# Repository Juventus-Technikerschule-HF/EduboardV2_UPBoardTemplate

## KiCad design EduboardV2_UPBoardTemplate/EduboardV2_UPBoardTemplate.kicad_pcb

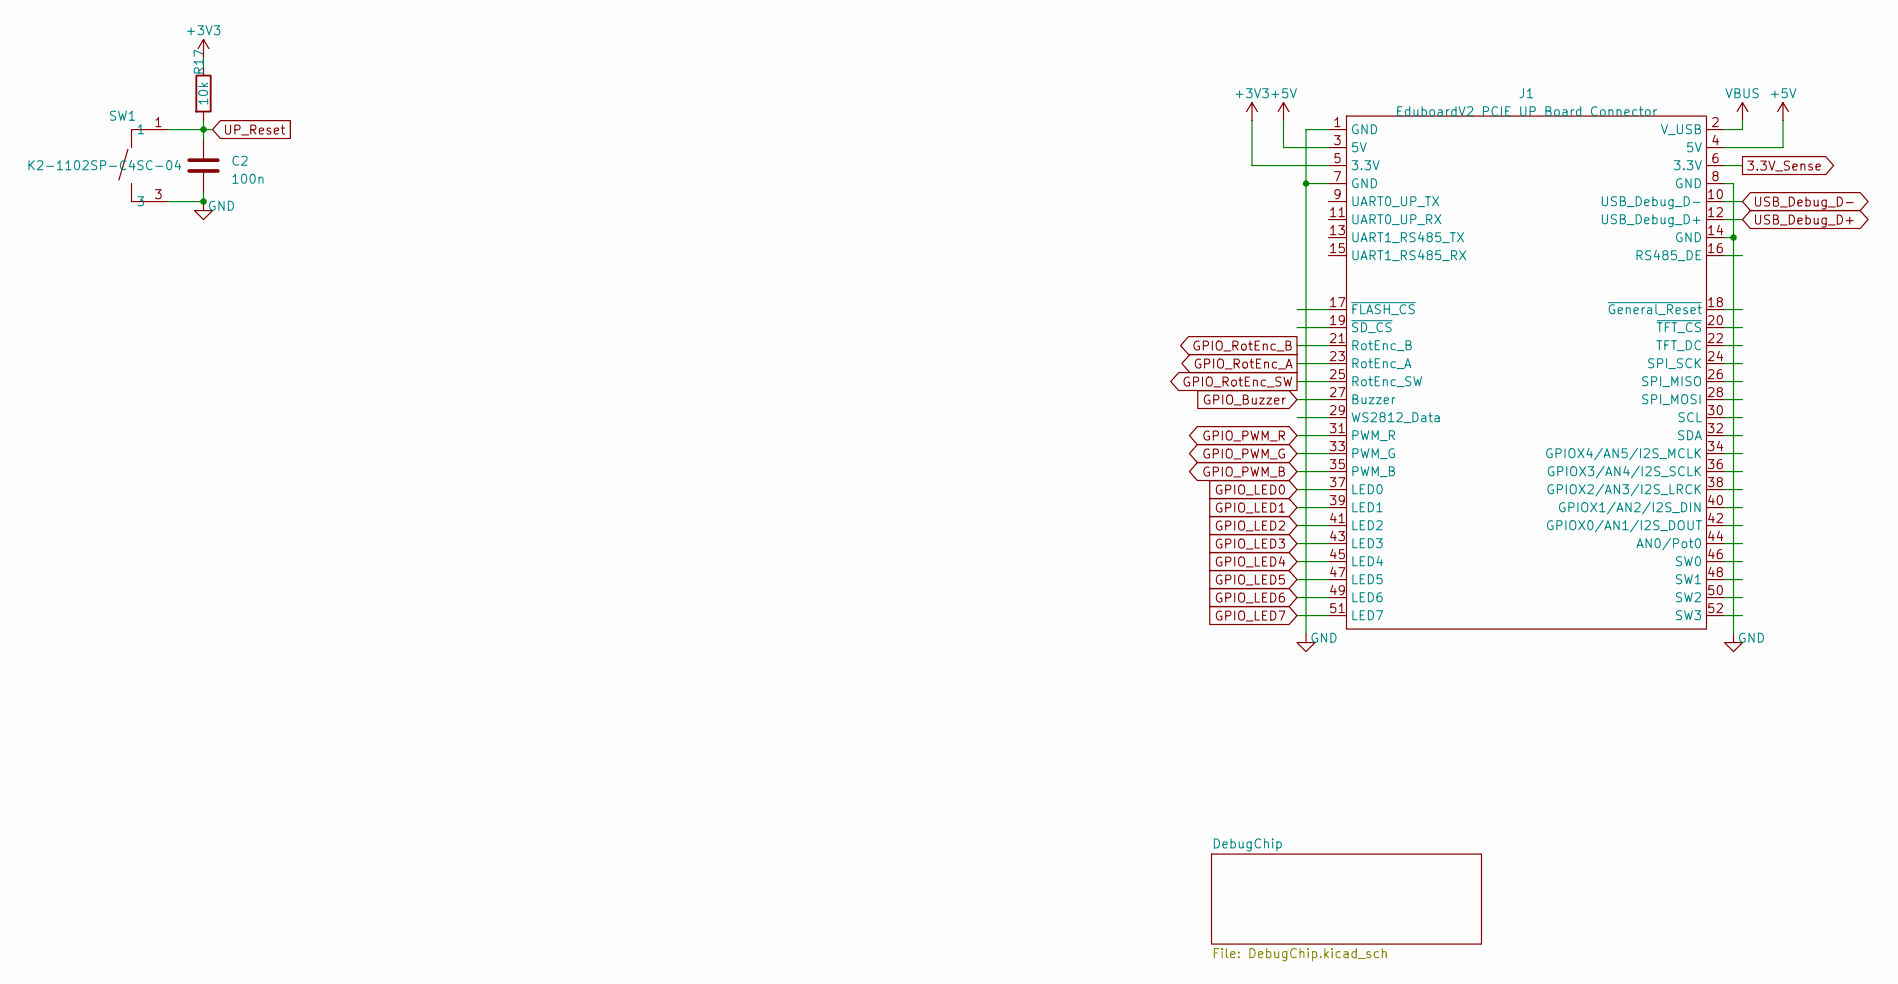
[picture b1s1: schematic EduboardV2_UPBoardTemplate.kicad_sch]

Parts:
C2: 100n; C_0603_1608Metric; JLCPCB Part # C105907
J1: EduboardV2 PCIE UP Board Connector; mini-PCIe_F1_Full
R17: 10k; R_0603_1608Metric; JLCPCB Part # C116677
SW1: K2-1102SP-C4SC-04; KEY-SMD_4P-L6.0-W6.0-P4.50-LS9.5-BL; LCSC Part C127509

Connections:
3.3V_Sense: J1.6 (3.3V); also elsewhere on the board
+3V3: J1.5 (3.3V); also elsewhere on the board
+5V: J1.3 (5V), J1.4 (5V)
GND: J1.1 (GND), J1.7 (GND), J1.8 (GND), J1.14 (GND), SW1.3, SW1.4; also elsewhere on the board
GPIO_Buzzer: J1.27 (Buzzer)
GPIO_LED0: J1.37 (LED0)
GPIO_LED1: J1.39 (LED1)
GPIO_LED2: J1.41 (LED2)
GPIO_LED3: J1.43 (LED3)
GPIO_LED4: J1.45 (LED4)
GPIO_LED5: J1.47 (LED5)
GPIO_LED6: J1.49 (LED6)
GPIO_LED7: J1.51 (LED7)
GPIO_PWM_B: J1.35 (PWM_B)
GPIO_PWM_G: J1.33 (PWM_G)
GPIO_PWM_R: J1.31 (PWM_R)
GPIO_RotEnc_A: J1.23 (RotEnc_A)
GPIO_RotEnc_B: J1.21 (RotEnc_B)
GPIO_RotEnc_SW: J1.25 (RotEnc_SW)
UP_Reset: SW1.1, SW1.2; also elsewhere on the board
USB_Debug_D+: J1.12 (USB_Debug_D+); also elsewhere on the board
USB_Debug_D-: J1.10 (USB_Debug_D-); also elsewhere on the board
VBUS: J1.2 (V_USB); also elsewhere on the board

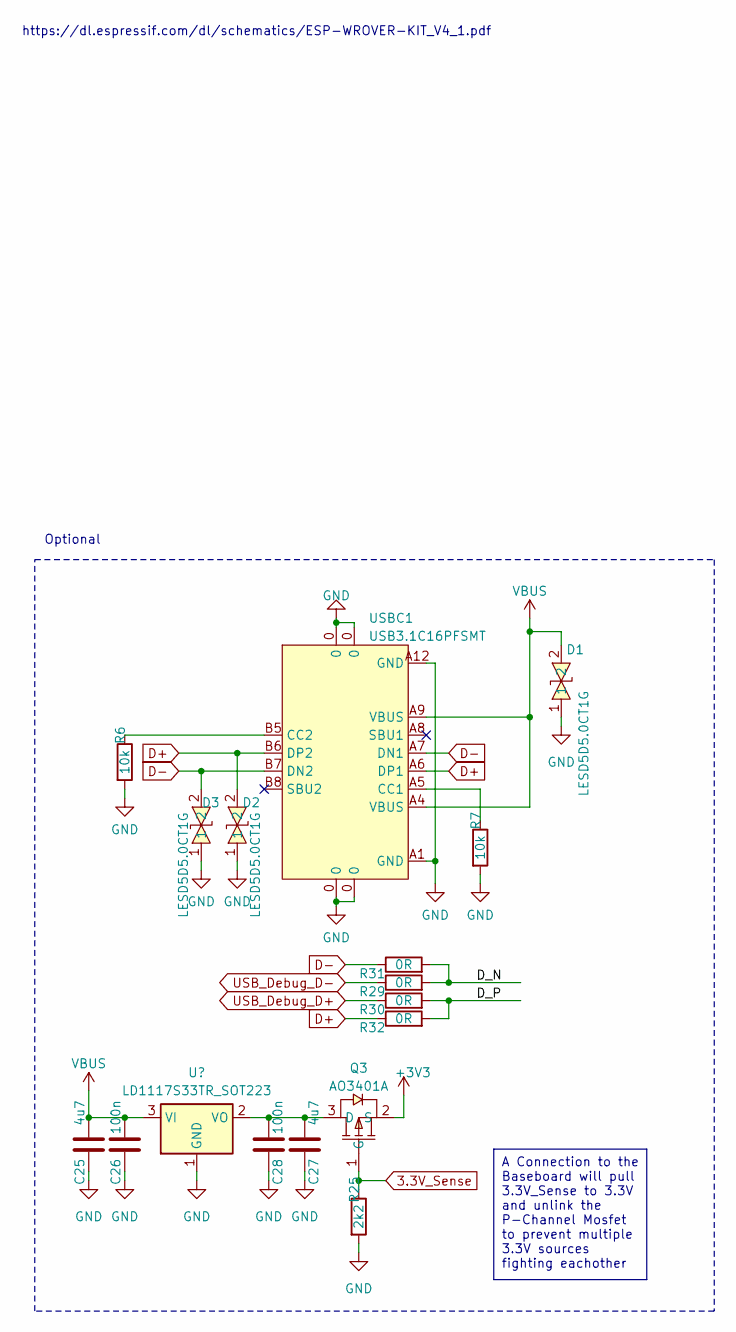
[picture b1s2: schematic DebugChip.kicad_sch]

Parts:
C25, C27: 4u7; C_0805_2012Metric; JLCPCB Part # C76642
C26, C28: 100n; C_0603_1608Metric; JLCPCB Part # C105907
D1, D2, D3: LESD5D5.0CT1G; SOD-523_L1.2-W0.8-LS1.6-BI; LCSC Part C383211
Q3: AO3401A; SOT-23_L2.9-W1.3-P1.90-LS2.4-BR; MPN AO3401A; LCSC Part C15127
R6, R7: 10k; R_0603_1608Metric; JLCPCB Part # C116677
R25: 2k2; R_0603_1608Metric; JLCPCB Part # C115003
R29, R30, R31, R32: 0R; R_0603_1608Metric; JLCPCB Part # C465460
U5: LD1117S33TR_SOT223; SOT-223-3_TabPin2; JLCPCB Part # C86781
USBC1: USB3.1C16PFSMT; USB-C-SMD_TYPE-C-USB-17; LCSC Part C167321

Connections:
3.3V_Sense: Q3.1 (G), R25.1; also elsewhere on the board
+3V3: Q3.2 (S); also elsewhere on the board
/DebugChip/D_N: R29.2, R31.2
/DebugChip/D_P: R30.2, R32.2
D+: D2.2, R32.1, USBC1.A6 (DP1), USBC1.B6 (DP2)
D-: D3.2, R31.1, USBC1.A7 (DN1), USBC1.B7 (DN2)
GND: C25.1, C26.1, C27.1, C28.1, D1.1, D2.1, D3.1, R6.2, R7.2, R25.2, U5.1 (GND), USBC1.0, USBC1.A1 (GND), USBC1.A12 (GND); also elsewhere on the board
unnamed: C27.2, C28.2, Q3.3 (D), U5.2 (VO)
unnamed: R7.1, USBC1.A5 (CC1)
unnamed: R6.1, USBC1.B5 (CC2)
USB_Debug_D+: R30.1; also elsewhere on the board
USB_Debug_D-: R29.1; also elsewhere on the board
VBUS: C25.2, C26.2, D1.2, U5.3 (VI), USBC1.A4 (VBUS), USBC1.A9 (VBUS); also elsewhere on the board

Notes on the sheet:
A Connection to the Baseboard will pull 3.3V_Sense to 3.3V and unlink the P-Channel Mosfet to prevent multiple 3.3V sources fighting eachother
Optional
https://dl.espressif.com/dl/schematics/ESP-WROVER-KIT_V4_1.pdf

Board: 4 copper layers, 21 parts (0 on the bottom side), 15 nets, no tracks yet.

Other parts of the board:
C17: 100n; C_0603_1608Metric
R19: 10k; R_0603_1608Metric

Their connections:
+3V3: R19.1; also elsewhere on the board
GND: C17.2; also elsewhere on the board
UP_Reset: C17.1, R19.2; also elsewhere on the board

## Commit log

2023-04-22 create template for UP Boards
2023-04-25 add .gitignore and delete untracked files
